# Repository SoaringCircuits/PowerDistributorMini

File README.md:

# PowerDistributor -mini-

## General remarks
This small board is designed to simplify and organize the wiring in your glider.
A pair of terminals is provided for each device to be connected, one each for the device and the associated fuse.
Up to 8 individual devices can be connected.

The board and terminals are designed for a much higher electrical load than should ever be needed in a glider, at least 10 Amps per channel and in total.

## Electrical installation
Integrating the board into the cabling is extremely simple.
For each device to be connected, there is a terminal for the device itself and the associated fuse.
This keeps the wiring harness simple and flexible; changes to devices or fuses do not require any adjustments to the circuits of other devices.
The wiring is shown in the following diagram.

## Wago Terminals

All terminals are easy to operate, just push the actuator with a little screwdriver and push-in or pull-out the conductor.

The terminals for fuses and devices are suitable for various types of wires:
- Solid concductor 0.2 - 1.5 mm^2
- Fine-stranded conductor 0.2 - 1.5 mm^2
- Fine-stranded conductor with ferrule 0.25 - 1.0 mm^2

The terminal for the main supply can handle conductors up to:
- Solid concductor 0.1 - 4.0 mm^2
- Fine-stranded conductor 0.1 - 4.0 mm^2
- Fine-stranded conductor with ferrule 0.25 - 2.5 mm^2

## Mechanical installation

The half housing is 3D-printed and reliably protects against short circuits on the contacts on the underside of the board.
With four mounting holes for M3 screws, the board can be securely and firmly mounted in the aircraft, with the screws fixing both the housing and the board at the same time.

## Disclaimer
Installation and use of the board are the sole responsibility of the user.
The board has been built to the best of our knowledge and belief, but no warranty or guarantee can be given for correct functioning or interference immunity.
The legal usability must be checked before each individual installation and, in case of doubt, clarified with competent and authorized personnel (CFS).

## Licence
Copyright Fabian Schöttler 2023.

This source describes Open Hardware and is licensed under the CERN-OHL-P
v2 or later.

You may redistribute and modify this documentation and make products
using it under the terms of the CERN-OHL-P v2 or later (https:/cern.ch/cern-ohl).
This documentation is distributed WITHOUT ANY EXPRESS OR IMPLIED
WARRANTY, INCLUDING OF MERCHANTABILITY, SATISFACTORY QUALITY
AND FITNESS FOR A PARTICULAR PURPOSE.
Please see the CERN-OHL-P v2 for applicable conditions

## Contact
If you have any questions or suggestions about the board, please send an e-mail to fabian@schoettlerhome.de.

------
Electrical and PCB design by [ScotteC](https://github.com/ScotteC)

Housing design by [Turbo87](https://github.com/Turbo87)

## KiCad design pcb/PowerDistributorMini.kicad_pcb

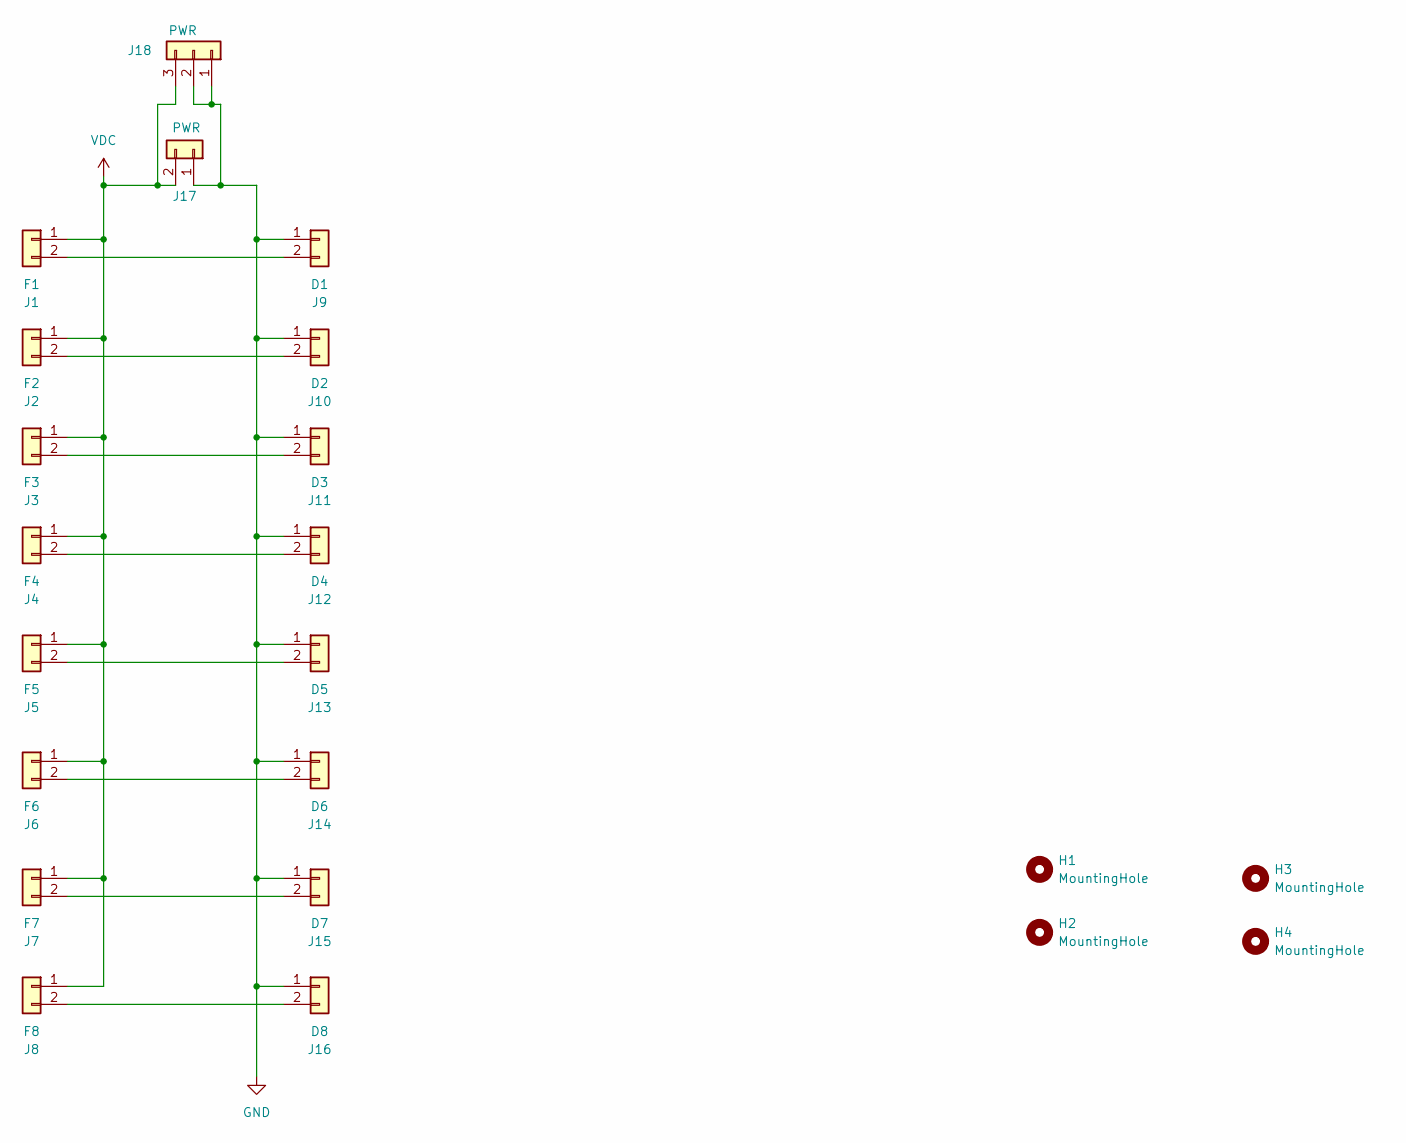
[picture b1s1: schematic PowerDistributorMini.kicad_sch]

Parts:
H1, H2, H3, H4: MountingHole; MountingHole_3.2mm_M3
J1: F1; Wago-250-202
J2: F2; Wago-250-202
J3: F3; Wago-250-202
J4: F4; Wago-250-202
J5: F5; Wago-250-202
J6: F6; Wago-250-202
J7: F7; Wago-250-202
J8: F8; Wago-250-202
J9: D1; Wago-250-202
J10: D2; Wago-250-202
J11: D3; Wago-250-202
J12: D4; Wago-250-202
J13: D5; Wago-250-202
J14: D6; Wago-250-202
J15: D7; Wago-250-202
J16: D8; Wago-250-202
J17: PWR; Wago-745-102
J18: PWR; Wago-250-203

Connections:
GND: J9.1, J10.1, J11.1, J12.1, J13.1, J14.1, J15.1, J16.1, J17.1, J18.1, J18.2
unnamed: J1.2, J9.2
unnamed: J2.2, J10.2
unnamed: J3.2, J11.2
unnamed: J4.2, J12.2
unnamed: J5.2, J13.2
unnamed: J6.2, J14.2
unnamed: J7.2, J15.2
unnamed: J8.2, J16.2
VDC: J1.1, J2.1, J3.1, J4.1, J5.1, J6.1, J7.1, J8.1, J17.2, J18.3

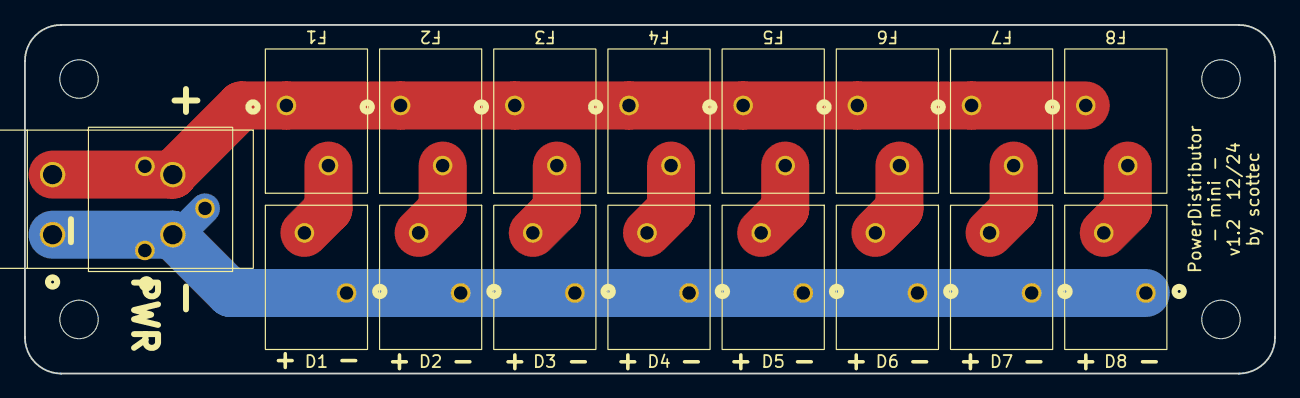
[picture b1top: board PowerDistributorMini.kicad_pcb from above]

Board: 2 copper layers, 104.0 x 29.0 mm, 22 parts (0 on the bottom side), 10 nets.

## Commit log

2023-12-20 v1.1
2023-12-24 change power connector, add markings, logos and measurements
2024-07-31 rename
2024-07-31 restructure, add case (3mf)
2024-08-14 add docu
2024-08-14 kicad 7.0 -> 8.0
2024-12-13 v1.2 : alterative main connector; some markings
